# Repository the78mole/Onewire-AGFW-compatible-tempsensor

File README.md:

# Onewire-AGFW-compatible-tempsensor

This is a AGFW-compatible Tempsensor for a 5x45mm (5x50) Housing

If you ever wanted to add a tempsensor to your heating pipes, the only way to do this efficiently and easily is, 
to attach it to the pipe and insulate it properly. But the respone time is less than optimal. A more efficient way
is to use direct immersive sensors, like heat meters do. For this heat meters, you can buy ball valves with a M10x1
opening, where AGFW direct immersed sensor perfectly fit in. These sensors are usually 5,0 x 45 mm or 5,2 x 45 mm.

But if you want to use a 1-wire DS18B20, you can only find 6 mm stainless stell sensors. This is mainly because the standard
cases for DS18B20 is a TO-92 case, which will never fit into a 5 mm tube. But there is the DB18B20U, that is fittet into a uMAX8 (or uSOP-8)
packages, that perfectly fits into the tube, but it needs some support from a PCB to be usable.

This is, what this repo is for. You will find 3D-Models, the schematics, the PCB design files and some specs, how the tube needs to be pressed.

Later, I'll also provide the CAD files for some tools to aid in pressing the steel tube correctly.

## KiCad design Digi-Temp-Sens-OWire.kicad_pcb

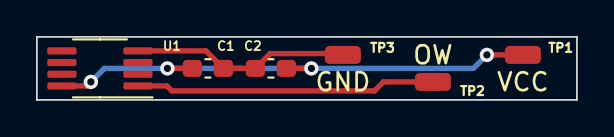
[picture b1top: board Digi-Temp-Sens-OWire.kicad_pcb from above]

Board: 2 copper layers, 30.0 x 3.5 mm, 6 parts (0 on the bottom side), 3 nets.

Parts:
C1, C2: 100n; C_0603_1608Metric_Pad1.08x0.95mm_HandSolder
TP1: VCC; SolderWirePad_1x01_SMD_1x2mm
TP2: OW; SolderWirePad_1x01_SMD_1x2mm
TP3: GND; SolderWirePad_1x01_SMD_1x2mm
U1: DS18B20U; MSOP-8_3x3mm_P0.65mm

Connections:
+5V: C1.1, C2.1, TP1.1, U1.8 (VDD)
/OW: TP2.1, U1.1 (DQ)
GND: C1.2, C2.2, TP3.1, U1.4 (GND)

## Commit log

2022-12-04 Create LICENSE
    Added the CERN Open Hardware License
2022-12-04 Added some images
2023-05-30 Added Gerber files
